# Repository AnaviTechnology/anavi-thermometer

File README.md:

# ANAVI Thermometer

ANAVI Thermometer is an open source hardware development board that acts like a WiFi smart thermometer. It features:

* ESP8266 WiFi microcontroller
* DHT22 sensor for temperature and humidity
* Terminal for waterproof DS18B20 1-Wire temperature sensor
* Dedicated slot for I2C OLED display
* Slots for up to 3 plug and play I2C sensors for temperature, barometric pressure, humidity and light
* UART (Universal asynchronous receiver/transmitter) pins for debugging

The default open source firmware for ANAVI Thermometer written as an [Arduino sketch is also available at GitHub](https://github.com/AnaviTechnology/anavi-thermometer-sw).

# License

The project is released under the [Creative Commons Attribution-ShareAlike 4.0 International (CC BY-SA 4.0)](https://creativecommons.org/licenses/by-sa/4.0/).

Note: This is a human-readable summary of (and not a substitute for) the [license](https://creativecommons.org/licenses/by-sa/4.0/legalcode).

You are free to:

Share — copy and redistribute the material in any medium or format Adapt — remix, transform, and build upon the material for any purpose, even commercially. The licensor cannot revoke these freedoms as long as you follow the license terms. Under the following terms:

Attribution — You must give appropriate credit, provide a link to the license, and indicate if changes were made. You may do so in any reasonable manner, but not in any way that suggests the licensor endorses you or your use. ShareAlike — If you remix, transform, or build upon the material, you must distribute your contributions under the same license as the original. No additional restrictions — You may not apply legal terms or technological measures that legally restrict others from doing anything the license permits. Notices:

You do not have to comply with the license for elements of the material in the public domain or where your use is permitted by an applicable exception or limitation. No warranties are given. The license may not give you all of the permissions necessary for your intended use. For example, other rights such as publicity, privacy, or moral rights may limit how you use the material.

You will have to provide a link to the original creator of the project http://www.anavi.technology on any documentation or website.

Credit can be attributed through a link to the creator website: http://www.anavi.technology

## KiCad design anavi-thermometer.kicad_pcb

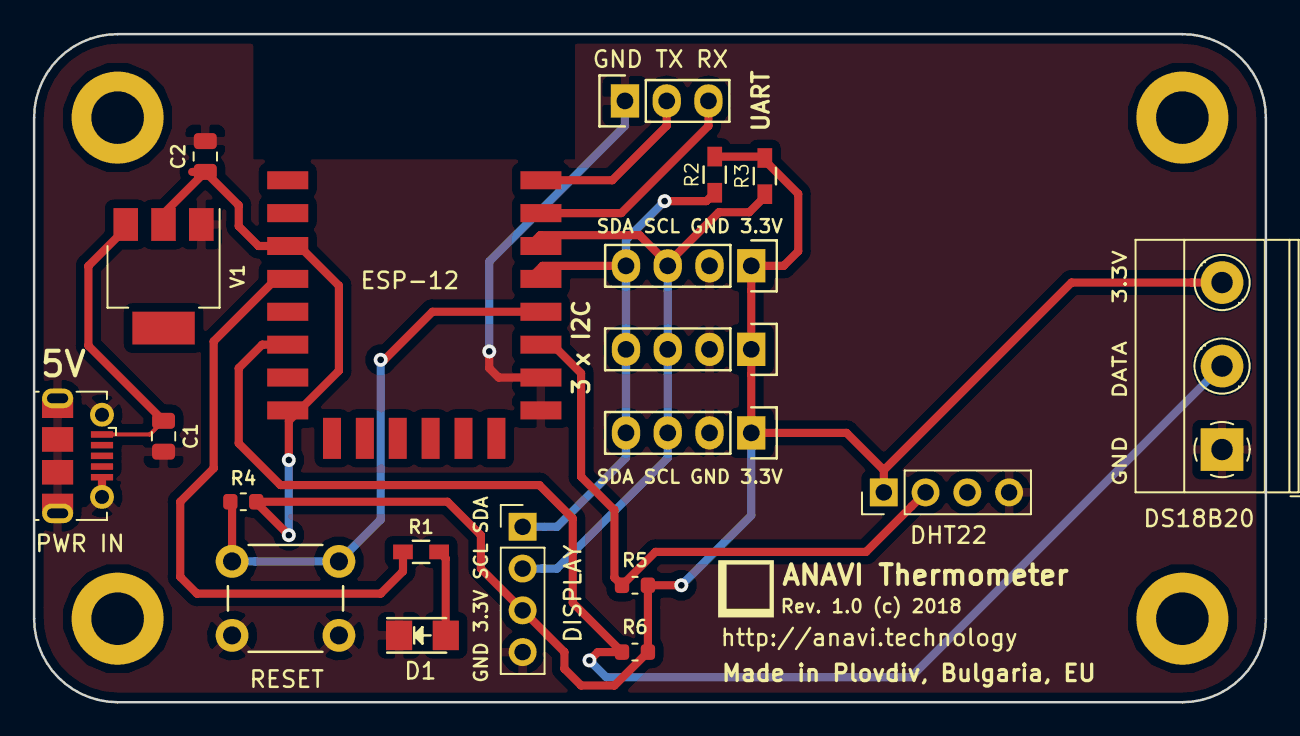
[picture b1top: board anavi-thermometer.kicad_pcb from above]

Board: 2 copper layers, 74.9 x 40.6 mm, 20 parts (0 on the bottom side), 12 nets.

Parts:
C1, C2: 10uF; C_0805_2012Metric
D1: LED; LED_1206
DHT22: DHT22; PinHeader_1x04_P2.54mm_Vertical
DISPLAY: Conn_01x04; PinHeader_1x04_P2.54mm_Vertical
DS18B20: DS18B20; TerminalBlock_Phoenix_MKDS-1,5-3-5.08_1x03_P5.08mm_Horizont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
ESP-12: ESP-12E; ESP-12E_SMD
P1: CONN_01X03; Pin_Header_Straight_1x03
PWR IN: USB_B_Micro; USB_Micro-B_Molex-105017-0001
R1: 68R; R_0603_HandSoldering
R2, R3: 4,7K; R_0603_HandSoldering
R4: 2K; R_0603_1608Metric
R5: 10K; R_0603_1608Metric
R6: 4,7K; R_0603_1608Metric
RESET: SW_DIP_x01; SW_PUSH_6mm_h4.3mm
U1, U2, U3: I2C_SENS_1; Pin_Header_Straight_1x04
V1: LD1117S33TR; SOT-223

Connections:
+3V3: C2.1, DHT22.1, DISPLAY.3, DS18B20.3, ESP-12.3, ESP-12.8, R2.1, R3.1, R4.2, R5.1, R6.1, U1.1, U2.1, U3.1, V1.2
+5V: C1.1, PWR IN.1, V1.3
GND: C1.2, C2.2, D1.1, DHT22.4, DISPLAY.4, DS18B20.1, ESP-12.9, ESP-12.10, P1.1, PWR IN.5, PWR IN.6, RESET.1, U1.2, U2.2, U3.2, V1.1
unnamed: D1.2, R1.2
unnamed: ESP-12.4, R1.1
unnamed: DS18B20.2, ESP-12.6, R6.2
unnamed: DHT22.2, ESP-12.11, R5.2
unnamed: ESP-12.12, R4.1, RESET.2
unnamed: DISPLAY.1, ESP-12.13, R2.2, U1.4, U2.4, U3.4
unnamed: DISPLAY.2, ESP-12.14, R3.2, U1.3, U2.3, U3.3
unnamed: ESP-12.15, P1.3
unnamed: ESP-12.16, P1.2

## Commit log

2018-09-21 anavi-thermometer: Intial commit
2018-09-21 anavi-thermometer.kicad_pcb: Update silkscreen
    Move the contour of DHT22 to the fab layer.
2018-09-24 anavi-thermometer.kicad_pcb: Update silkscreen
2018-09-29 anavi-thermometer.kicad_pcb: Fix UART silkscreen
    Fix silkscreen for UART.
2018-10-09 anavi-thermometer.kicad_pcb: Assembly guidelines
    Add guidelines for easier SMT assembly.
2019-02-17 README.md: Fix title
    Set proper title and other minor improvements.
    Suggested-by: Karl Schuh <k.schuh@schuh-tv.at>
2020-03-23 README.md: Fix broken link to the Arduino sketch
    Fix broken link and add details.

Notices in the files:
anavi-thermometer.kicad_pcb:
Rev. 1.0 (c) 2018
